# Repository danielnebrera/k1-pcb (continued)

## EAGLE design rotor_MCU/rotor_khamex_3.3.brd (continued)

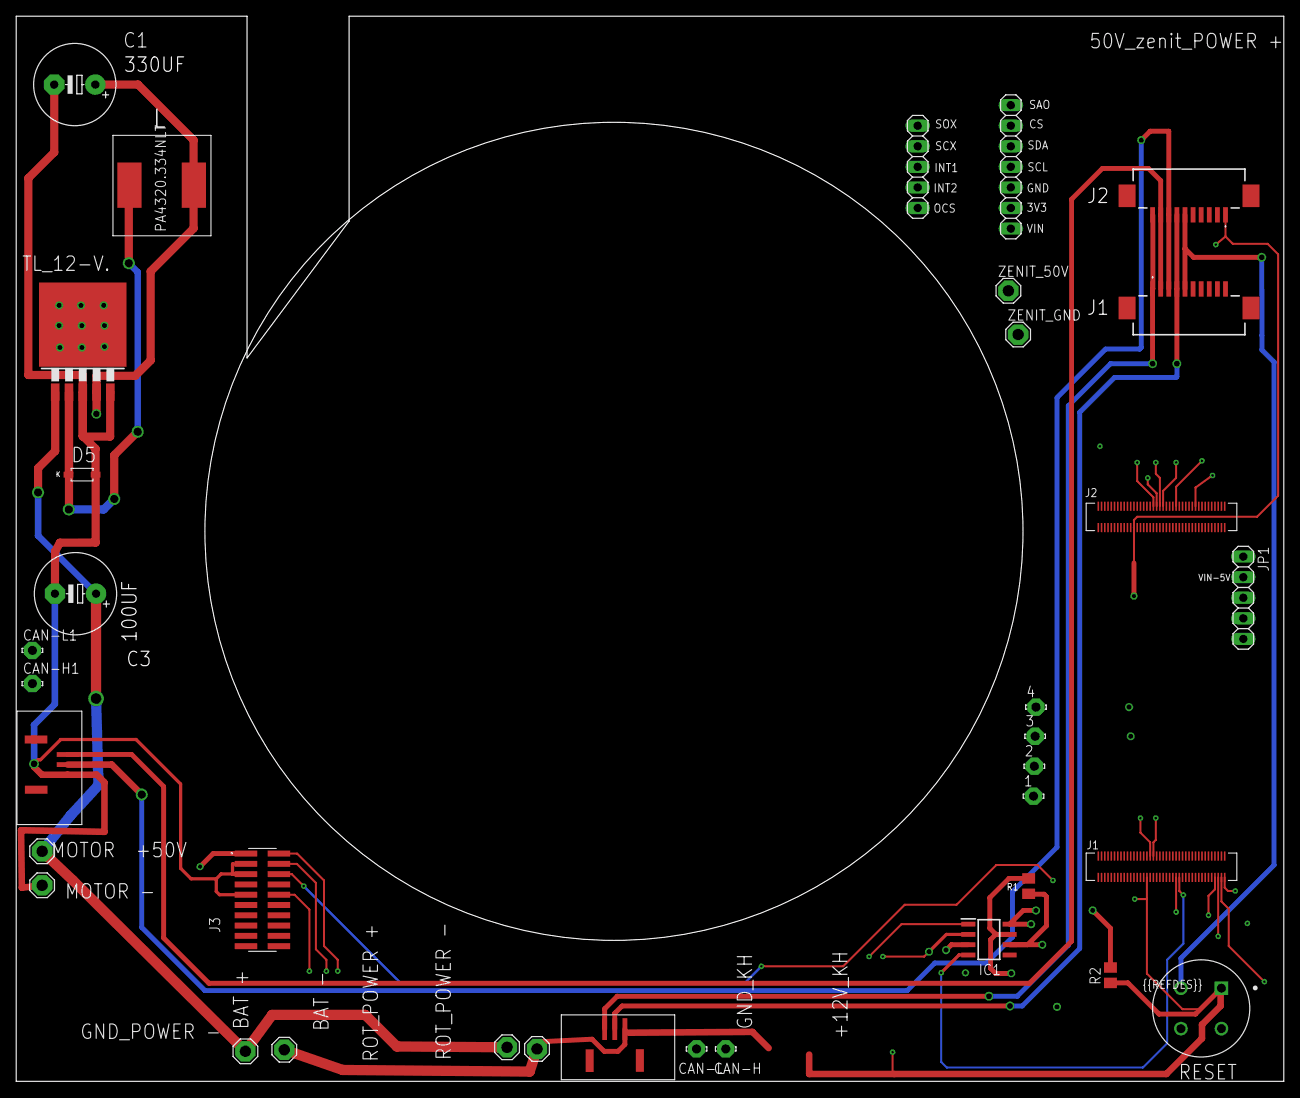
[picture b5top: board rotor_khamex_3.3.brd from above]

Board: 4 copper layers, 156.5 x 131.5 mm, 35 parts (0 on the bottom side), 27 nets.
